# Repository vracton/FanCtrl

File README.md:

# CopyPad

An ESP32-powered adapter/cover for the Lutron Maestro Fan Control and Light Dimmer that allows for smart functionality, i.e. toggling on and off from a phone.

## Features

- **Wireless Connectivity**: Connect to the switch through Blynk from anywhere
- **Double Solenoid**: Control both switches - extremely quickly
- **Double Click**: Supports double click to set switch to max

*physical picture available soon!!*

## Project Structure

```
FanCtrl/
├── README.md  
├── JOURNAL.md               
├── cad/                    
│   └── FanCtrl.step     
├── firmware/                
│   └── main.ino          
├── pcb/                    
│   ├── FanCtrl.kicad_pcb   
│   ├── FanCtrl.kicad_sch   
│   ├── FanCtrl.kicad_pro   
│   ├── FanCtrl.kicad_prl
└── production/             
    ├── FanCtrl_Baseplate.stl    
    ├── FanCtrl_Cover.stl     
    ├── gerber.zip         
    └── bom.csv
```

## Assembly

1. Solder all components according to the schematic
2. Flash `main.ino` to the microcontroller
3. 3D print the case files from `production/FanCtrl_Baseplate.stl ` and `production/FanCtrl_Cover.stl`
4. Install the PCB into the case
5. Secure the top case with heatset inserts and screws

## Bill of Materials

| Component | Quantity | Description |
|-----------|----------|-------------|
| PCB | 1 | Manufactured from provided Gerber files |
| ESP32-C3 | 1 |  |
| IRLZ44N MOSFETs | 2 |  |
| CR2032 Coin Cell Batteries | 2 | 3v |
| CR2032 Battery Holder | 1 |  |
| Solenoid | 2 | 5v |
| MT3608 DC/DC Step Up Converter | 2x | 3.3v -> 5v |
| Case | 1 | 3D printed from provided STL files |
| Heatset Inserts | 4 | M3x5mx4mm |
| Screws | 4 | M3x16mm |
| Soldering Iron | 1 | For Assembly |
| 220 ohm Resistors | 2 

## Pictures

## License

This project is open source and available under the MIT License. See the LICENSE file for more details.

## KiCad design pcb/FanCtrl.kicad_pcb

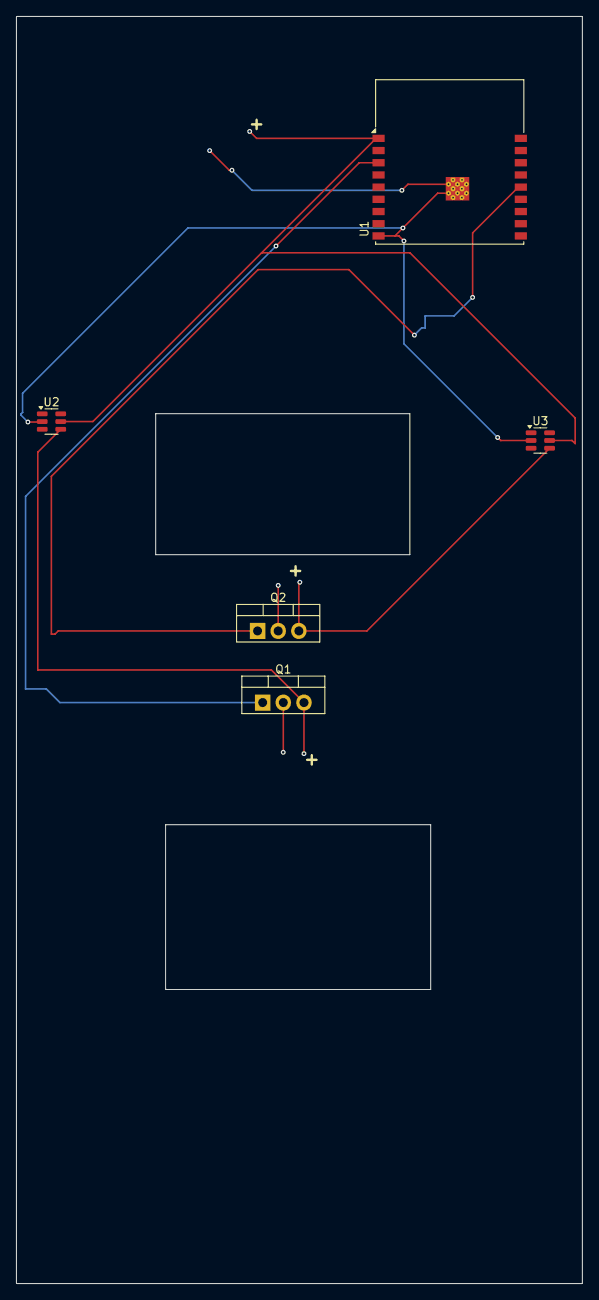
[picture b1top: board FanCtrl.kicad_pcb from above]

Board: 2 copper layers, 69.6 x 155.8 mm, 5 parts (0 on the bottom side), 6 nets.

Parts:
Q1, Q2: IRLZ44N; TO-220-3_Vertical
U1: ESP32-C3-WROOM-02
U2, U3: MT3608; SOT-23-6

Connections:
unnamed: U1.1 (3V3), U2.5 (IN), U3.5 (IN)
unnamed: U1.9 (GND), U1.19 (GND), U2.2 (GND), U3.2 (GND)
unnamed: Q1.1 (G), U1.3 (IO4)
unnamed: Q1.3 (S), U2.4 (EN)
unnamed: Q2.1 (G), U1.14 (IO19)
unnamed: Q2.3 (S), U3.4 (EN)

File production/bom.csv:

count,item,price,link
1,PCB,38.42,JLCPCB
1,ESP32-C3,3.37,https://www.aliexpress.us/item/3256808882566983.html
2,IRLZ44N MOSFETs,2.59,https://www.aliexpress.us/item/3256807952109860.html
2,CR2032 Coin Cell Batteries,4.99,https://www.amazon.com/Procter-Gamble-DURDL2032B4PK-Duracell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
2,CR2032 Battery Holder,2.34,https://www.aliexpress.us/item/3256807747963704.html
2,Solenoid,3.30,https://www.aliexpress.us/item/3256809098511002.html
2,MT3608 DC/DC Step Up Converter,1.39,https://www.aliexpress.us/item/3256808096223695.html
1,Case,Shipping (~5),Printing Legion
4,Heatset Inserts,2.47,https://www.aliexpress.us/item/3256808480358197.html
4,Screws M3x16mm,1.96,https://www.aliexpress.us/item/3256807797167765.html
,total,62.40,

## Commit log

2025-08-01 code
2025-08-01 README
2025-08-01 Journal
2025-08-03 actual final version
2025-08-08 actually actually final version
